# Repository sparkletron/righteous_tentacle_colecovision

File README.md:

# Righteous Tentacle, Colecovision Reverse Engineering Project
### Schematic and PCB reproduction.

---

  author: Jay Convertino

  date: 2023.03.01

  details: Reverse engineer original PCB to create a schematic and functional replacment board. This only includes the NTSC system.

  license: MIT

---

## LICENSE
  - All files related to or generated from the KiCAD source fall under the MIT license.
  - All files generated by me, Jay Convertino, fall under the MIT license.
  - All files from other sources fall under the license of their specification.

## RELEASE VERSIONS
### Current
  - 1.0.2.F - Fixed solder mask on expansion bay connector.

### Past
  - 1.0.1.F - Added power and reset switch to case.
  - 1.0.0.F - initial release of revision F main PCB
  - DEV

## Gerbers
  Files available below, to download select the download icon next to the raw icon on right hand upper side of the page.
  - [Main PCB Gerber Archive](schematic/PCB_TOOLS/gerber/MAIN_GERBER.zip)
  - [RF PCB Gerber Archive](schematic/PCB_TOOLS/gerber/RF_GERBER.zip)

## Wiki
  - Please see the [Wiki](../../wiki) for various information.
    - Contains howto's, build notes, bill of materials, project logs, and signal documentation.

## Parts list
  - [Link to Wiki Parts list for the original console](../../wiki/Detailed-Part-Listing-For-Original)
  - [Link to Wiki Parts list for ordering parts](../../wiki/Detailed-Part-Listing-For-Orders)

## Intro

  This recreation of the PCB is for documenation, and reproduction purposes. This mimicks the PCB of the original NTSC revision F main board.

## SOURCES
### Schematic Check
  - Atari HQ Schematic : https://wiki.console5.com/wiki/Colecovision : Dan Boris
  - Atari Age : https://forums.atariage.com/topic/285656-new-colecovision-schematics/ : ChildOfCV

  Special thanks to ChildOfCV. Using his as a check for mine after buzzing out my own board was a great help. His schematic on
  its own is a great resource.

  Did find a few issues with mine vs the ChildOfCV version, my board is a different revision so they will differ in subtle ways.
  Seems to be mostly just cap and resistor values in the RF circuit. Though I did adjust my values on the clock to reflect those
  recommend in the tech manual.

  The Dan Boris schematic is ok, has a few mistakes that I can't recall at the moment. Mentioning it since I did look at it, but
  due to its issues I didn't use it.

## REQUIREMENTS
  - KiCAD v7.X

## BUILD TIPS
  This design is made so anyone can build this. You may send it out to a fab house, you may use a PCB mill, or even etch it.
  This is possible since the components can serve as the plated through hole. Other holes can simply have a solid piece of
  wire inserted and soldered to complete the connection (excess resistor leads is a great option).

  Recommend soldering the cartridge connector first, the CPU makes soldering one side of the pins a bit difficult to do
  without melting the connector.

  There are various questionable routings, these are how the original is done. Some adjustments were made to make some things easier
  for at home builders without plated through holes.

## FILE INFORMATION
  - README.md, is this file.
  - LICENSE.md, is the license file (MIT) for anything create by me, Jay Convertion, that resides in this repository.
  - doc, contains various documents used.
    - datasheets, contains parts used on the original board.
    - refs, sources used for checks
      - Coleco_ADAM_Schematic_-_Delta_Game.png, publicly available schematic of the ADAM
      - Coleco.zip, ChildOfCV schematic for the console and other various parts of the colecovision.
      - colecovision_atari_hq_schematic.pdf, Colecovision console schematic... has errors.
      - tms-doc-annotated.pdf, TMS design document corrected by Nicholas Piegdon
  - models, PCB items and case designes
    - component_search_engine, website 3D files
    - FreeCAD
      - MainBoard, 3D PCB export to step using freecad instead of kicad.
      - parts, parts designed for the PCB by myself and future contributions.
    - inventor_2024
      - base_case, contains ipt/stl files for building a case for the colecovision.
      - OldVersions, inventor files
    - partcommunity, website 3D files
    - kicad, kicad 3D pcb export to step.
  - pics, images take by me or others(watermark added) of the colecovision.
    - 3D, images generated by modeling tools.
    - built, contains all PCBs built
    - build_case, contains all completed cases with PCB.
    - control_pcb, pics of a different Colecovision console pcb (different REV) for comparison.
    - control_unit, pics of a different Colecovision console for comparison.
    - outside_sources, external sources with added watermark.
    - reverse_high_res, scans from a Canon 9600 DPI flatbed scanner of the PCB boards. Compressed to save space.
    - tear_down, images of the parts as they came apart.
    - signals
      - digital, all digital analyzer captures
      - analog, all analog scope captures
  - schematic, contains KiCAD schematic files.
    - coleco_original.kicad_pro, this file is the main project file that contains EVERTHING.
    - *-backups, are folders KiCAD creates to backup the project.
    - PCB_TOOLS
      - gerber, containts all exports from KiCAD
        - main, base PCB
        - rf, modulator PCB
      - GIMP_Placement_Tool, gimp project used to help place parts in the correct locations.
      - main, contains the main PCB extracted from the main project for production.
      - rf, contains RF PCB extracted from the main project for production.
    - lib, external components for KiCAD
      - CONNECTOR_PCBEdge_EXT
      - LOGOS
      - MHPS2273
      - MODELS
      - MOUNTS
      - OS102011MA1QN1
      - PADS
      - POWER_SYMBOLS
      - RCJ-041
      - RF_MODULATORS
      - SWITCHES_THT
      - TE_550841-2
      - VARIABLE_INDUCTORS
      - VINTAGE_AUDIO_SYNTH
      - VINTAGE_RAM
      - VINTAGE_VDP
    - PDF, various KiCAD exports in the PDF format. PCB and/or schematics.

## PCB IMAGE

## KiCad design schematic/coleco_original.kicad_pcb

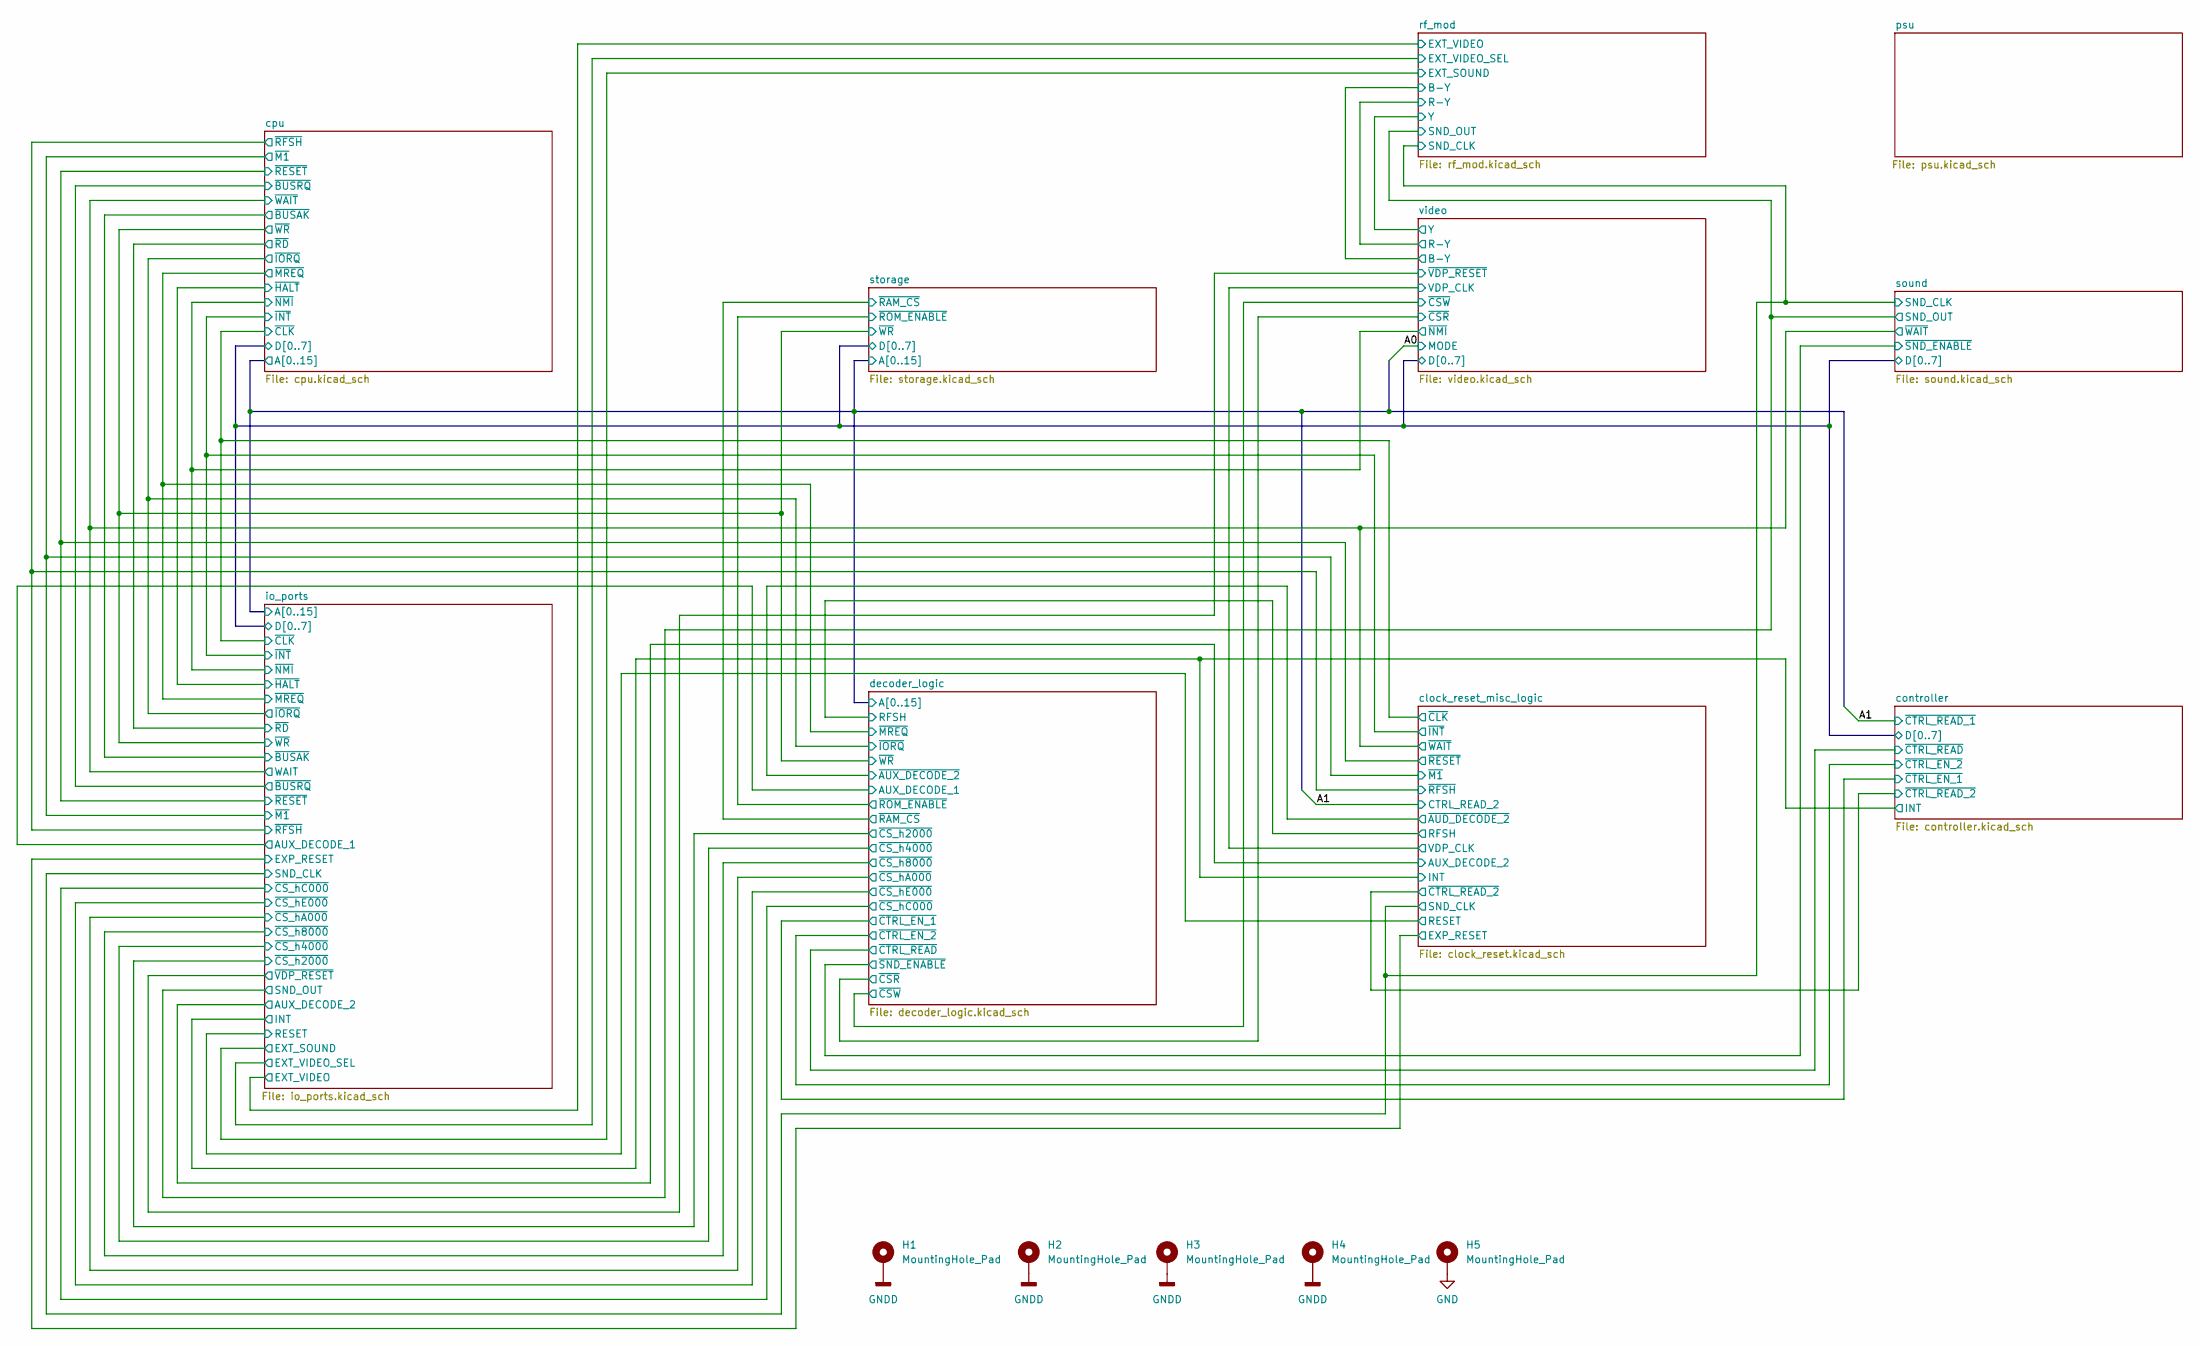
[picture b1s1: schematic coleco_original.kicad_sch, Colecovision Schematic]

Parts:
H1, H2, H3, H4, H5: MountingHole_Pad; MountingHole_5.3mm_M5_ISO14580_Pad

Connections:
GND: H5.1; also elsewhere on the board
GNDD: H1.1, H2.1, H3.1, H4.1; also elsewhere on the board

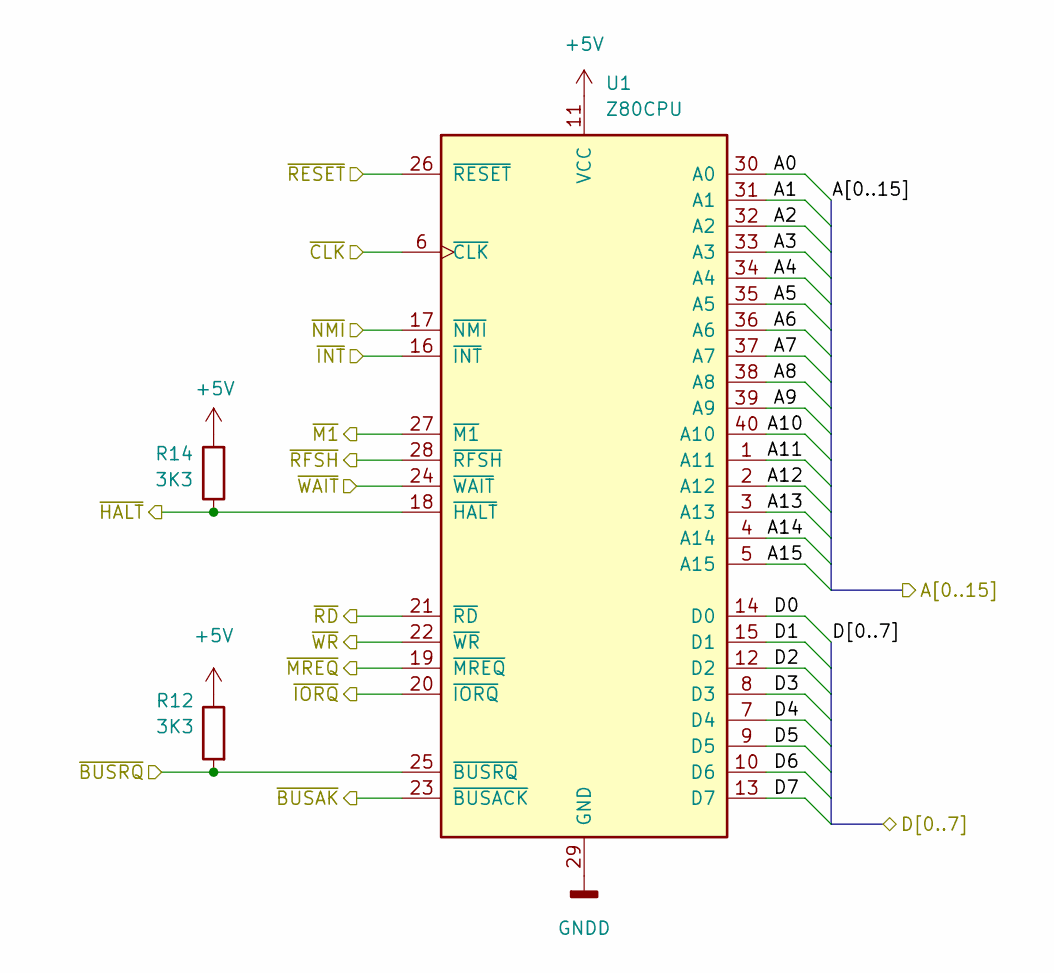
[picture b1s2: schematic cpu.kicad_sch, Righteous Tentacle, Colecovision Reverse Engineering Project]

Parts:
R12, R14: 3K3; R_Axial_DIN0207_L6.3mm_D2.5mm_P10.16mm_Horizontal
U1: Z80CPU; DIP-40_W15.24mm_LongPads

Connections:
+5V: R12.1, R14.2, U1.11 (VCC); also elsewhere on the board
/clock_reset_misc_logic/~CLK: U1.6 (~CLK); also elsewhere on the board
/clock_reset_misc_logic/~INT: U1.16 (~INT); also elsewhere on the board
/clock_reset_misc_logic/~M1: U1.27 (~M1); also elsewhere on the board
/clock_reset_misc_logic/~RESET: U1.26 (~RESET); also elsewhere on the board
/clock_reset_misc_logic/~RFSH: U1.28 (~RFSH); also elsewhere on the board
/clock_reset_misc_logic/~WAIT: U1.24 (~WAIT); also elsewhere on the board
/cpu/A0: U1.30 (A0); also elsewhere on the board
/cpu/A1: U1.31 (A1); also elsewhere on the board
/cpu/A2: U1.32 (A2); also elsewhere on the board
/cpu/A3: U1.33 (A3); also elsewhere on the board
/cpu/A4: U1.34 (A4); also elsewhere on the board
/cpu/A5: U1.35 (A5); also elsewhere on the board
/cpu/A6: U1.36 (A6); also elsewhere on the board
/cpu/A7: U1.37 (A7); also elsewhere on the board
/cpu/A8: U1.38 (A8); also elsewhere on the board
/cpu/A9: U1.39 (A9); also elsewhere on the board
/cpu/A10: U1.40 (A10); also elsewhere on the board
/cpu/A11: U1.1 (A11); also elsewhere on the board
/cpu/A12: U1.2 (A12); also elsewhere on the board
/cpu/A13: U1.3 (A13); also elsewhere on the board
/cpu/A14: U1.4 (A14); also elsewhere on the board
/cpu/A15: U1.5 (A15); also elsewhere on the board
/cpu/D0: U1.14 (D0); also elsewhere on the board
/cpu/D1: U1.15 (D1); also elsewhere on the board
/cpu/D2: U1.12 (D2); also elsewhere on the board
/cpu/D3: U1.8 (D3); also elsewhere on the board
/cpu/D4: U1.7 (D4); also elsewhere on the board
/cpu/D5: U1.9 (D5); also elsewhere on the board
/cpu/D6: U1.10 (D6); also elsewhere on the board
/cpu/D7: U1.13 (D7); also elsewhere on the board
/cpu/~BUSAK: U1.23 (~BUSACK); also elsewhere on the board
/cpu/~BUSRQ: R12.2, U1.25 (~BUSRQ); also elsewhere on the board
/cpu/~HALT: R14.1, U1.18 (~HALT); also elsewhere on the board
/cpu/~IORQ: U1.20 (~IORQ); also elsewhere on the board
/cpu/~MREQ: U1.19 (~MREQ); also elsewhere on the board
/cpu/~NMI: U1.17 (~NMI); also elsewhere on the board
/cpu/~RD: U1.21 (~RD); also elsewhere on the board
/cpu/~WR: U1.22 (~WR); also elsewhere on the board
GNDD: U1.29 (GND); also elsewhere on the board

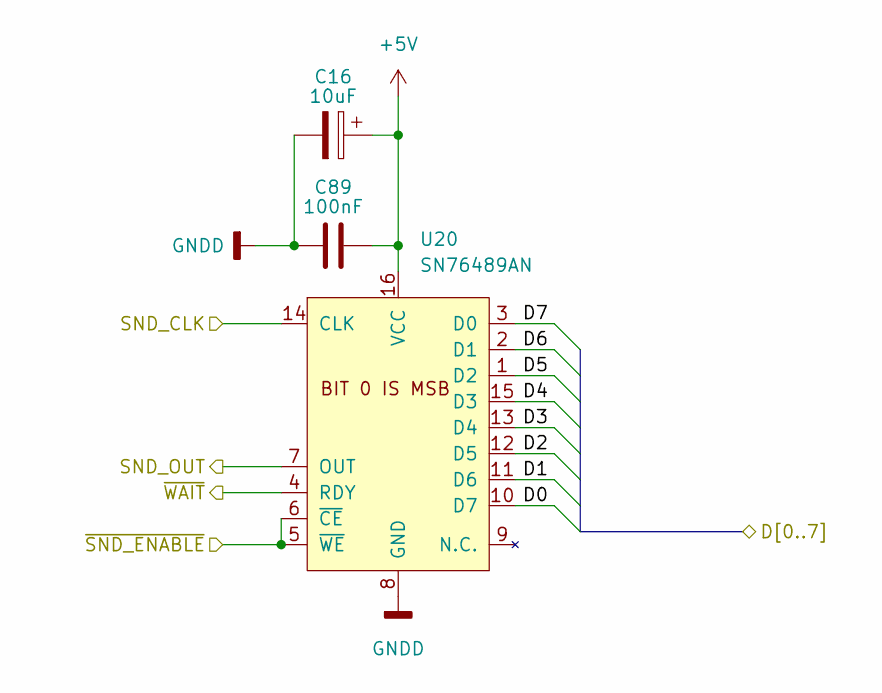
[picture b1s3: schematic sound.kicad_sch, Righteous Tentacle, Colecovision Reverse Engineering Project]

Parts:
C16: 10uF; CP_Radial_D8.0mm_P5.00mm
C89: 100nF; C_Disc_D7.0mm_W2.5mm_P5.00mm
U20: SN76489AN; DIP-16_W7.62mm_LongPads

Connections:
+5V: C16.1, C89.1, U20.16 (VCC); also elsewhere on the board
/clock_reset_misc_logic/SND_CLK: U20.14 (CLK); also elsewhere on the board
/clock_reset_misc_logic/~WAIT: U20.4 (RDY); also elsewhere on the board
/cpu/D0: U20.10 (D7); also elsewhere on the board
/cpu/D1: U20.11 (D6); also elsewhere on the board
/cpu/D2: U20.12 (D5); also elsewhere on the board
/cpu/D3: U20.13 (D4); also elsewhere on the board
/cpu/D4: U20.15 (D3); also elsewhere on the board
/cpu/D5: U20.1 (D2); also elsewhere on the board
/cpu/D6: U20.2 (D1); also elsewhere on the board
/cpu/D7: U20.3 (D0); also elsewhere on the board
/decoder_logic/~SND_ENABLE: U20.5 (~WE), U20.6 (~CE); also elsewhere on the board
/io_ports/SND_OUT: U20.7 (OUT); also elsewhere on the board
GNDD: C16.2, C89.2, U20.8 (GND); also elsewhere on the board

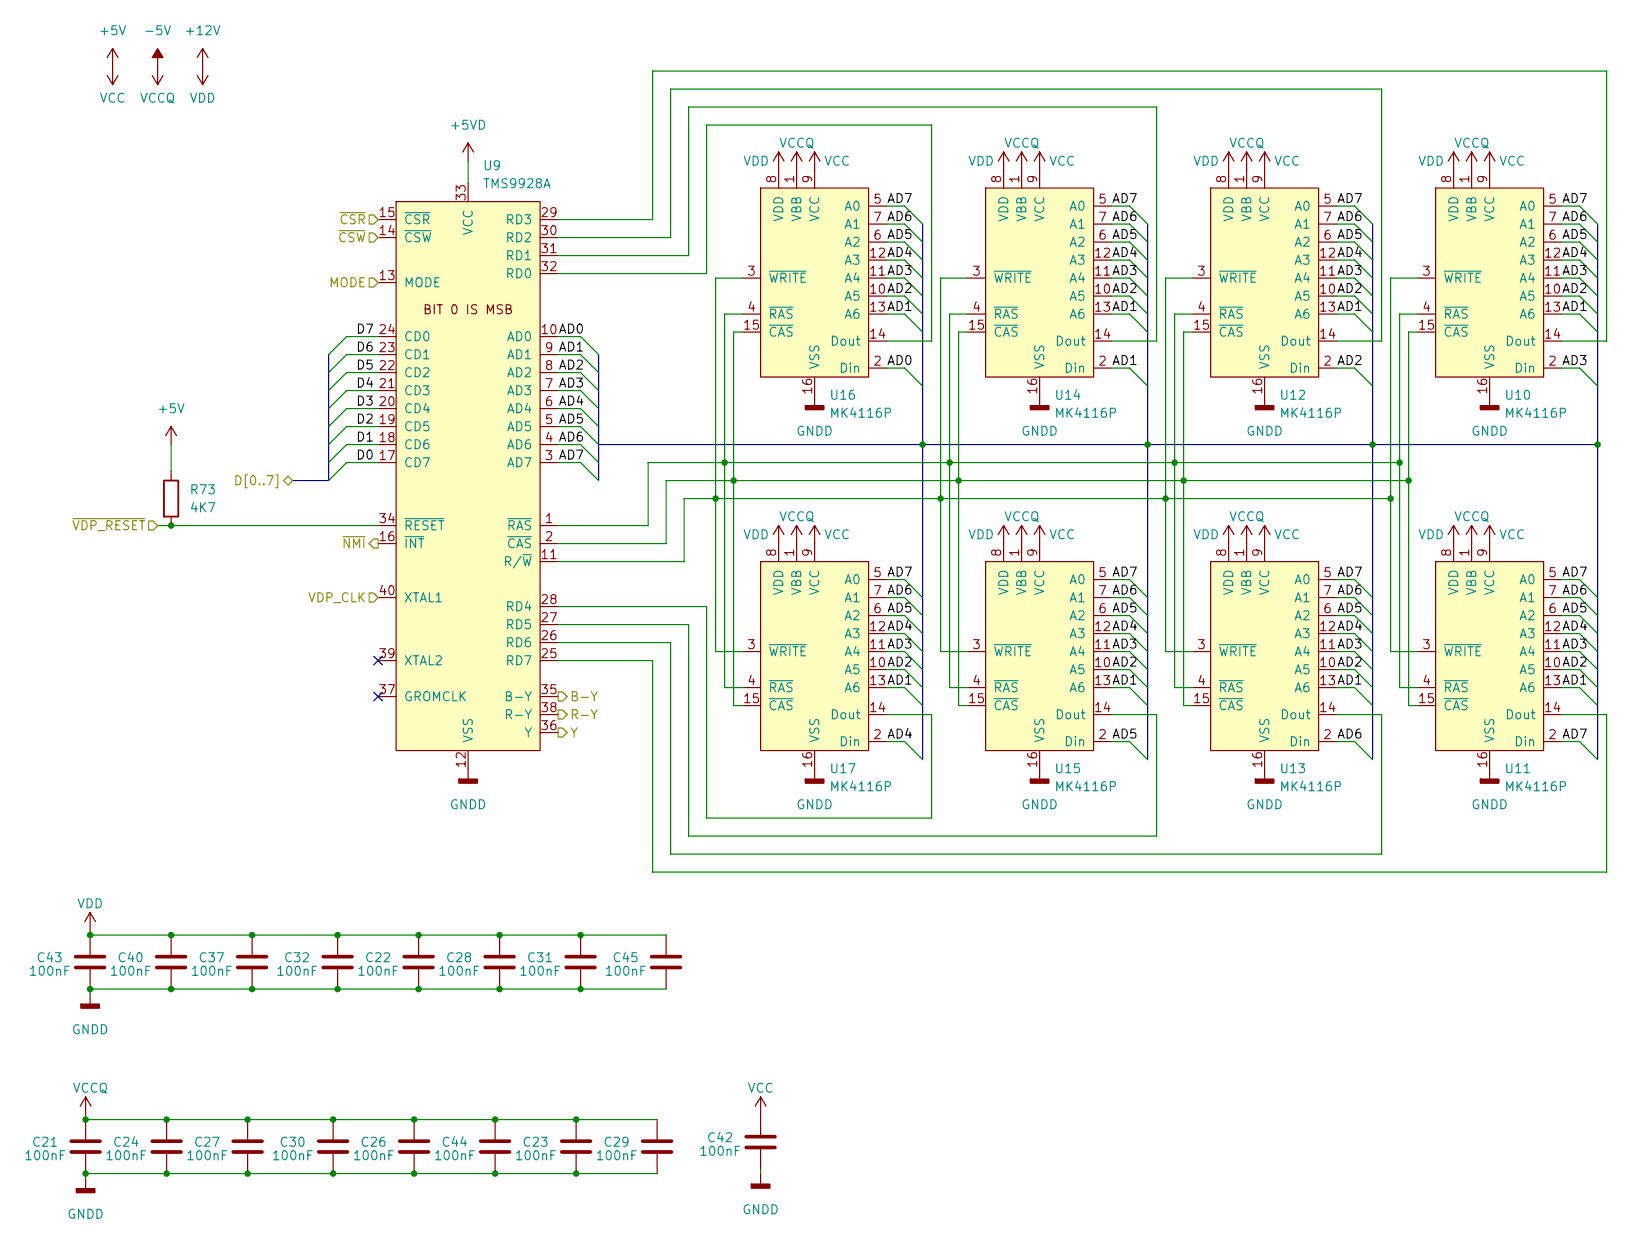
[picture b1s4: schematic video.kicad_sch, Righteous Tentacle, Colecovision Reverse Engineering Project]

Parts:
C21, C22, C23, C24, C26, C27, C28, C29, C30, C31, C32, C37, C40, C42, C43, C44, C45: 100nF; C_Disc_D7.0mm_W2.5mm_P5.00mm
R73: 4K7; R_Axial_DIN0207_L6.3mm_D2.5mm_P10.16mm_Horizontal
U9: TMS9928A; DIP-40_W15.24mm_LongPads
U10, U11, U12, U13, U14, U15, U16, U17: MK4116P; DIP-16_W7.62mm_LongPads

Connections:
+5V: C42.1, R73.1, U10.9 (VCC), U11.9 (VCC), U12.9 (VCC), U13.9 (VCC), U14.9 (VCC), U15.9 (VCC), U16.9 (VCC), U17.9 (VCC); also elsewhere on the board
+5VD: U9.33 (VCC); also elsewhere on the board
+12V: C22.1, C28.1, C31.1, C32.1, C37.1, C40.1, C43.1, C45.1, U10.8 (VDD), U11.8 (VDD), U12.8 (VDD), U13.8 (VDD), U14.8 (VDD), U15.8 (VDD), U16.8 (VDD), U17.8 (VDD); also elsewhere on the board
-5V: C21.1, C23.1, C24.1, C26.1, C27.1, C29.1, C30.1, C44.1, U10.1 (VBB), U11.1 (VBB), U12.1 (VBB), U13.1 (VBB), U14.1 (VBB), U15.1 (VBB), U16.1 (VBB), U17.1 (VBB); also elsewhere on the board
/clock_reset_misc_logic/VDP_CLK: U9.40 (XTAL1); also elsewhere on the board
/cpu/A0: U9.13 (MODE); also elsewhere on the board
/cpu/D0: U9.17 (CD7); also elsewhere on the board
/cpu/D1: U9.18 (CD6); also elsewhere on the board
/cpu/D2: U9.19 (CD5); also elsewhere on the board
/cpu/D3: U9.20 (CD4); also elsewhere on the board
/cpu/D4: U9.21 (CD3); also elsewhere on the board
/cpu/D5: U9.22 (CD2); also elsewhere on the board
/cpu/D6: U9.23 (CD1); also elsewhere on the board
/cpu/D7: U9.24 (CD0); also elsewhere on the board
/cpu/~NMI: U9.16 (~INT); also elsewhere on the board
/decoder_logic/~CSR: U9.15 (~CSR); also elsewhere on the board
/decoder_logic/~CSW: U9.14 (~CSW); also elsewhere on the board
/io_ports/~VDP_RESET: R73.2, U9.34 (~RESET); also elsewhere on the board
/rf_mod/B-Y: U9.35 (B-Y); also elsewhere on the board
/rf_mod/R-Y: U9.38 (R-Y); also elsewhere on the board
/rf_mod/Y: U9.36 (Y); also elsewhere on the board
/video/AD0: U9.10 (AD0), U16.2 (Din)
/video/AD1: U9.9 (AD1), U10.13 (A6), U11.13 (A6), U12.13 (A6), U13.13 (A6), U14.2 (Din), U14.13 (A6), U15.13 (A6), U16.13 (A6), U17.13 (A6)
/video/AD2: U9.8 (AD2), U10.10 (A5), U11.10 (A5), U12.2 (Din), U12.10 (A5), U13.10 (A5), U14.10 (A5), U15.10 (A5), U16.10 (A5), U17.10 (A5)
/video/AD3: U9.7 (AD3), U10.2 (Din), U10.11 (A4), U11.11 (A4), U12.11 (A4), U13.11 (A4), U14.11 (A4), U15.11 (A4), U16.11 (A4), U17.11 (A4)
/video/AD4: U9.6 (AD4), U10.12 (A3), U11.12 (A3), U12.12 (A3), U13.12 (A3), U14.12 (A3), U15.12 (A3), U16.12 (A3), U17.2 (Din), U17.12 (A3)
/video/AD5: U9.5 (AD5), U10.6 (A2), U11.6 (A2), U12.6 (A2), U13.6 (A2), U14.6 (A2), U15.2 (Din), U15.6 (A2), U16.6 (A2), U17.6 (A2)
/video/AD6: U9.4 (AD6), U10.7 (A1), U11.7 (A1), U12.7 (A1), U13.2 (Din), U13.7 (A1), U14.7 (A1), U15.7 (A1), U16.7 (A1), U17.7 (A1)
/video/AD7: U9.3 (AD7), U10.5 (A0), U11.2 (Din), U11.5 (A0), U12.5 (A0), U13.5 (A0), U14.5 (A0), U15.5 (A0), U16.5 (A0), U17.5 (A0)
GNDD: C21.2, C22.2, C23.2, C24.2, C26.2, C27.2, C28.2, C29.2, C30.2, C31.2, C32.2, C37.2, C40.2, C42.2, C43.2, C44.2, C45.2, U9.12 (VSS), U10.16 (VSS), U11.16 (VSS), U12.16 (VSS), U13.16 (VSS), U14.16 (VSS), U15.16 (VSS), U16.16 (VSS), U17.16 (VSS); also elsewhere on the board
unnamed: U9.11 (R/~W), U10.3 (~WRITE), U11.3 (~WRITE), U12.3 (~WRITE), U13.3 (~WRITE), U14.3 (~WRITE), U15.3 (~WRITE), U16.3 (~WRITE), U17.3 (~WRITE)
unnamed: U9.1 (~RAS), U10.4 (~RAS), U11.4 (~RAS), U12.4 (~RAS), U13.4 (~RAS), U14.4 (~RAS), U15.4 (~RAS), U16.4 (~RAS), U17.4 (~RAS)
unnamed: U9.29 (RD3), U10.14 (Dout)
unnamed: U9.2 (~CAS), U10.15 (~CAS), U11.15 (~CAS), U12.15 (~CAS), U13.15 (~CAS), U14.15 (~CAS), U15.15 (~CAS), U16.15 (~CAS), U17.15 (~CAS)
unnamed: U9.25 (RD7), U11.14 (Dout)
unnamed: U9.30 (RD2), U12.14 (Dout)
unnamed: U9.26 (RD6), U13.14 (Dout)
unnamed: U9.31 (RD1), U14.14 (Dout)
unnamed: U9.27 (RD5), U15.14 (Dout)
unnamed: U9.32 (RD0), U16.14 (Dout)
unnamed: U9.28 (RD4), U17.14 (Dout)

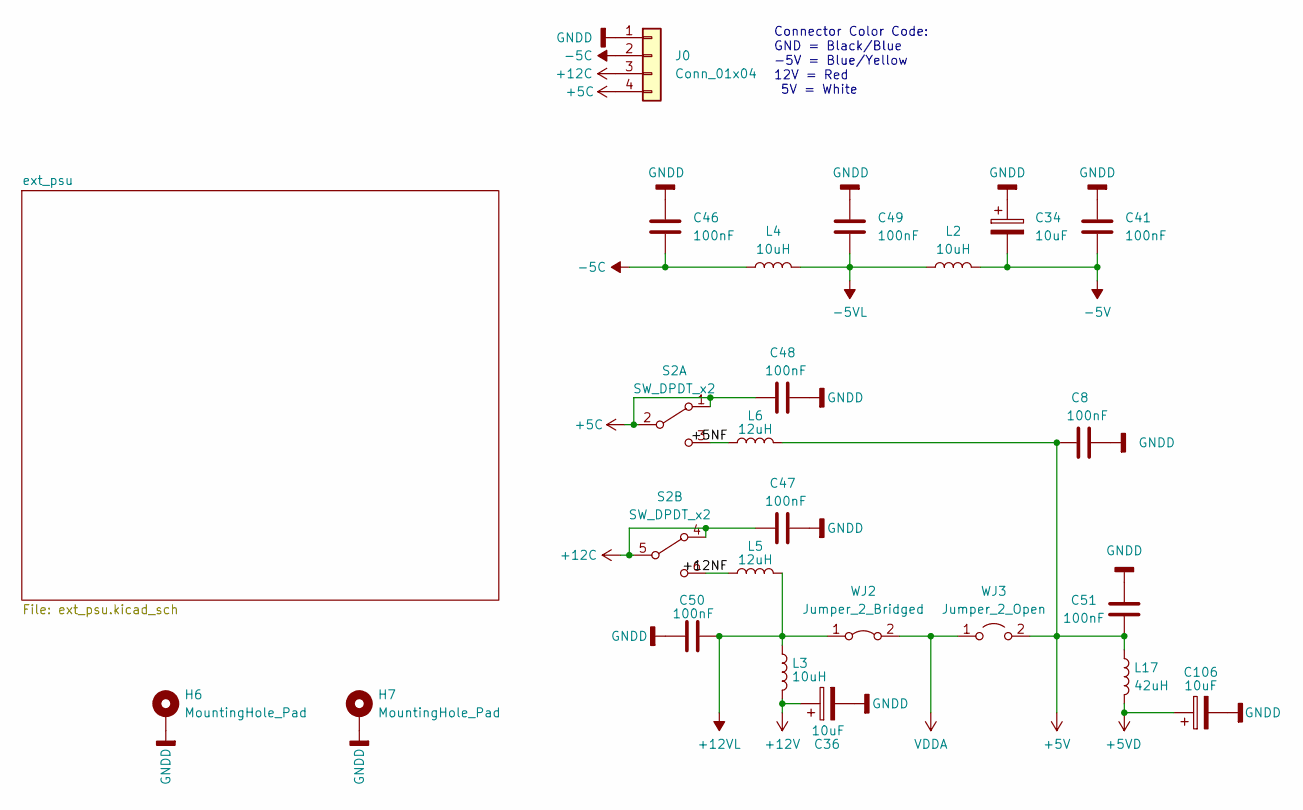
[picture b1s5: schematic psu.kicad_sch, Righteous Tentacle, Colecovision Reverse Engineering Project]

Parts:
C8, C41, C46, C47, C48, C49, C50, C51: 100nF; C_Disc_D7.0mm_W2.5mm_P5.00mm
C34, C36: 10uF; CP_Radial_D8.0mm_P5.00mm
C106: 10uF; CP_Radial_Tantal_D4.5mm_P2.50mm
H6, H7: MountingHole_Pad; SWITCH_MOUNT
J0: Conn_01x04; Molex_KK-396_A-41791-0004_1x04_P3.96mm_Vertical
L2, L3, L4: 10uH; L_Axial_L11.0mm_D4.5mm_P7.62mm_Vertical_Fastron_MECC
L5, L6: 12uH; L_Axial_L12.8mm_D5.8mm_P25.40mm_Horizontal_Fastron_HBCC
L17: 42uH; L_Axial_L11.0mm_D4.5mm_P7.62mm_Vertical_Fastron_MECC
S2: SW_DPDT_x2; DPDT_GF-626-0061
WJ2: Jumper_2_Bridged; R_Axial_DIN0207_L6.3mm_D2.5mm_P15.24mm_Horizontal
WJ3: Jumper_2_Open; R_Axial_DIN0207_L6.3mm_D2.5mm_P15.24mm_Horizontal

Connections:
+5C: C48.2, J0.4, S2.1 (A), S2.2 (B)
+5V: C8.2, C51.1, L6.2, L17.1, WJ3.2 (B); also elsewhere on the board
+5VD: C106.1, L17.2; also elsewhere on the board
+12C: C47.2, J0.3, S2.4 (A), S2.5 (B)
+12V: C36.1, L3.2; also elsewhere on the board
+12VL: C50.2, L3.1, L5.2, WJ2.1 (A); also elsewhere on the board
-5C: C46.2, J0.2, L4.1
-5V: C34.2, C41.2, L2.2; also elsewhere on the board
-5VL: C49.2, L2.1, L4.2; also elsewhere on the board
/psu/+5NF: L6.1, S2.3 (C)
/psu/+12NF: L5.1, S2.6 (C)
GNDD: C8.1, C34.1, C36.2, C41.1, C46.1, C47.1, C48.1, C49.1, C50.1, C51.2, C106.2, H6.1, H7.1, J0.1; also elsewhere on the board
VDDA: WJ2.2 (B), WJ3.1 (A); also elsewhere on the board

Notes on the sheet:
Connector Color Code: GND = Black/Blue -5V = Blue/Yellow 12V = Red 5V = White

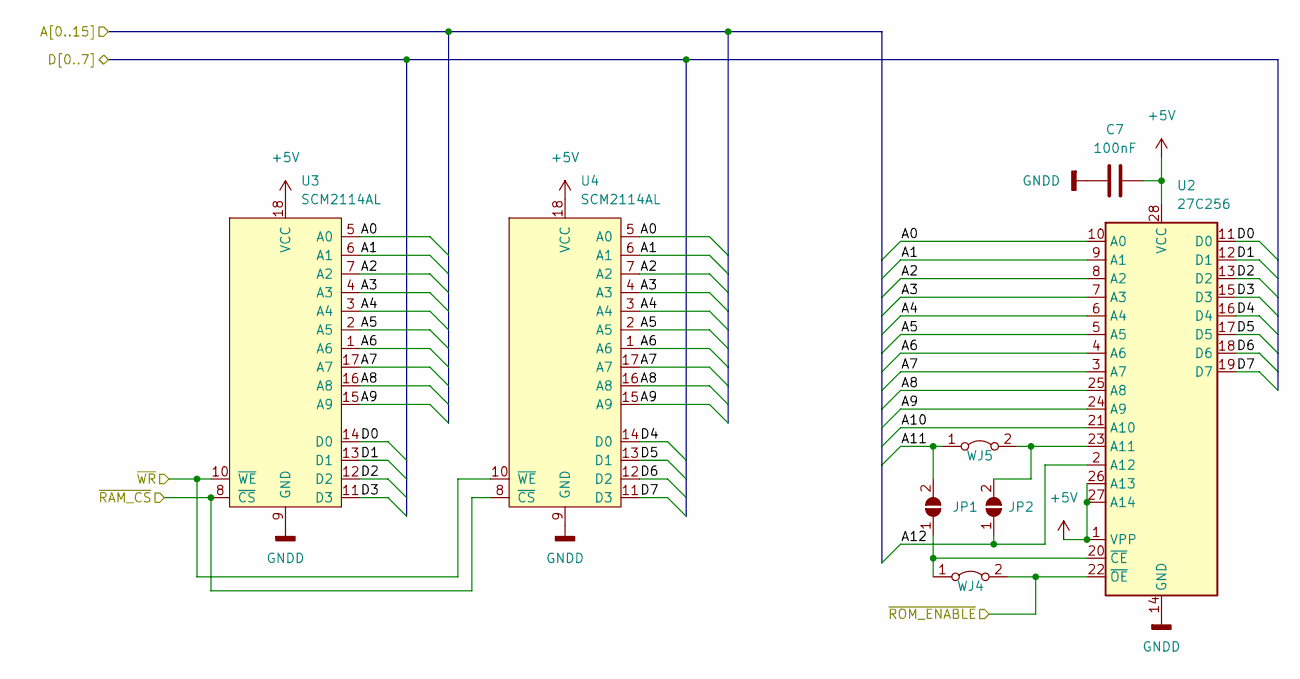
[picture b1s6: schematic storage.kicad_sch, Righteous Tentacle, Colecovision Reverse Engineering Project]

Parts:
C7: 100nF; C_Disc_D7.0mm_W2.5mm_P5.00mm
JP1, JP2: SolderJumper_2_Open; SolderJumper-2_P1.3mm_Open_Pad1.0x1.5mm
U2: 27C256; DIP-28_W15.24mm
U3, U4: SCM2114AL; DIP-18_W7.62mm_LongPads
WJ4, WJ5: Jumper_2_Bridged_32K_ROM; R_Axial_DIN0207_L6.3mm_D2.5mm_P15.24mm_Horizontal

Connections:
+5V: C7.1, U2.1 (VPP), U2.26 (A13), U2.27 (A14), U2.28 (VCC), U3.18 (VCC), U4.18 (VCC); also elsewhere on the board
/cpu/A0: U2.10 (A0), U3.5 (A0), U4.5 (A0); also elsewhere on the board
/cpu/A1: U2.9 (A1), U3.6 (A1), U4.6 (A1); also elsewhere on the board
/cpu/A2: U2.8 (A2), U3.7 (A2), U4.7 (A2); also elsewhere on the board
/cpu/A3: U2.7 (A3), U3.4 (A3), U4.4 (A3); also elsewhere on the board
/cpu/A4: U2.6 (A4), U3.3 (A4), U4.3 (A4); also elsewhere on the board
/cpu/A5: U2.5 (A5), U3.2 (A5), U4.2 (A5); also elsewhere on the board
/cpu/A6: U2.4 (A6), U3.1 (A6), U4.1 (A6); also elsewhere on the board
/cpu/A7: U2.3 (A7), U3.17 (A7), U4.17 (A7); also elsewhere on the board
/cpu/A8: U2.25 (A8), U3.16 (A8), U4.16 (A8); also elsewhere on the board
/cpu/A9: U2.24 (A9), U3.15 (A9), U4.15 (A9); also elsewhere on the board
/cpu/A10: U2.21 (A10); also elsewhere on the board
/cpu/A11: JP1.2 (B), WJ5.1 (A); also elsewhere on the board
/cpu/A12: JP2.1 (A), U2.2 (A12); also elsewhere on the board
/cpu/D0: U2.11 (D0), U3.14 (D0); also elsewhere on the board
/cpu/D1: U2.12 (D1), U3.13 (D1); also elsewhere on the board
/cpu/D2: U2.13 (D2), U3.12 (D2); also elsewhere on the board
/cpu/D3: U2.15 (D3), U3.11 (D3); also elsewhere on the board
/cpu/D4: U2.16 (D4), U4.14 (D0); also elsewhere on the board
/cpu/D5: U2.17 (D5), U4.13 (D1); also elsewhere on the board
/cpu/D6: U2.18 (D6), U4.12 (D2); also elsewhere on the board
/cpu/D7: U2.19 (D7), U4.11 (D3); also elsewhere on the board
/cpu/~WR: U3.10 (~WE), U4.10 (~WE); also elsewhere on the board
/decoder_logic/~RAM_CS: U3.8 (~CS), U4.8 (~CS); also elsewhere on the board
/decoder_logic/~ROM_ENABLE: U2.22 (~OE), WJ4.2 (B); also elsewhere on the board
GNDD: C7.2, U2.14 (GND), U3.9 (GND), U4.9 (GND); also elsewhere on the board
unnamed: JP1.1 (A), U2.20 (~CE), WJ4.1 (A)
unnamed: JP2.2 (B), U2.23 (A11), WJ5.2 (B)

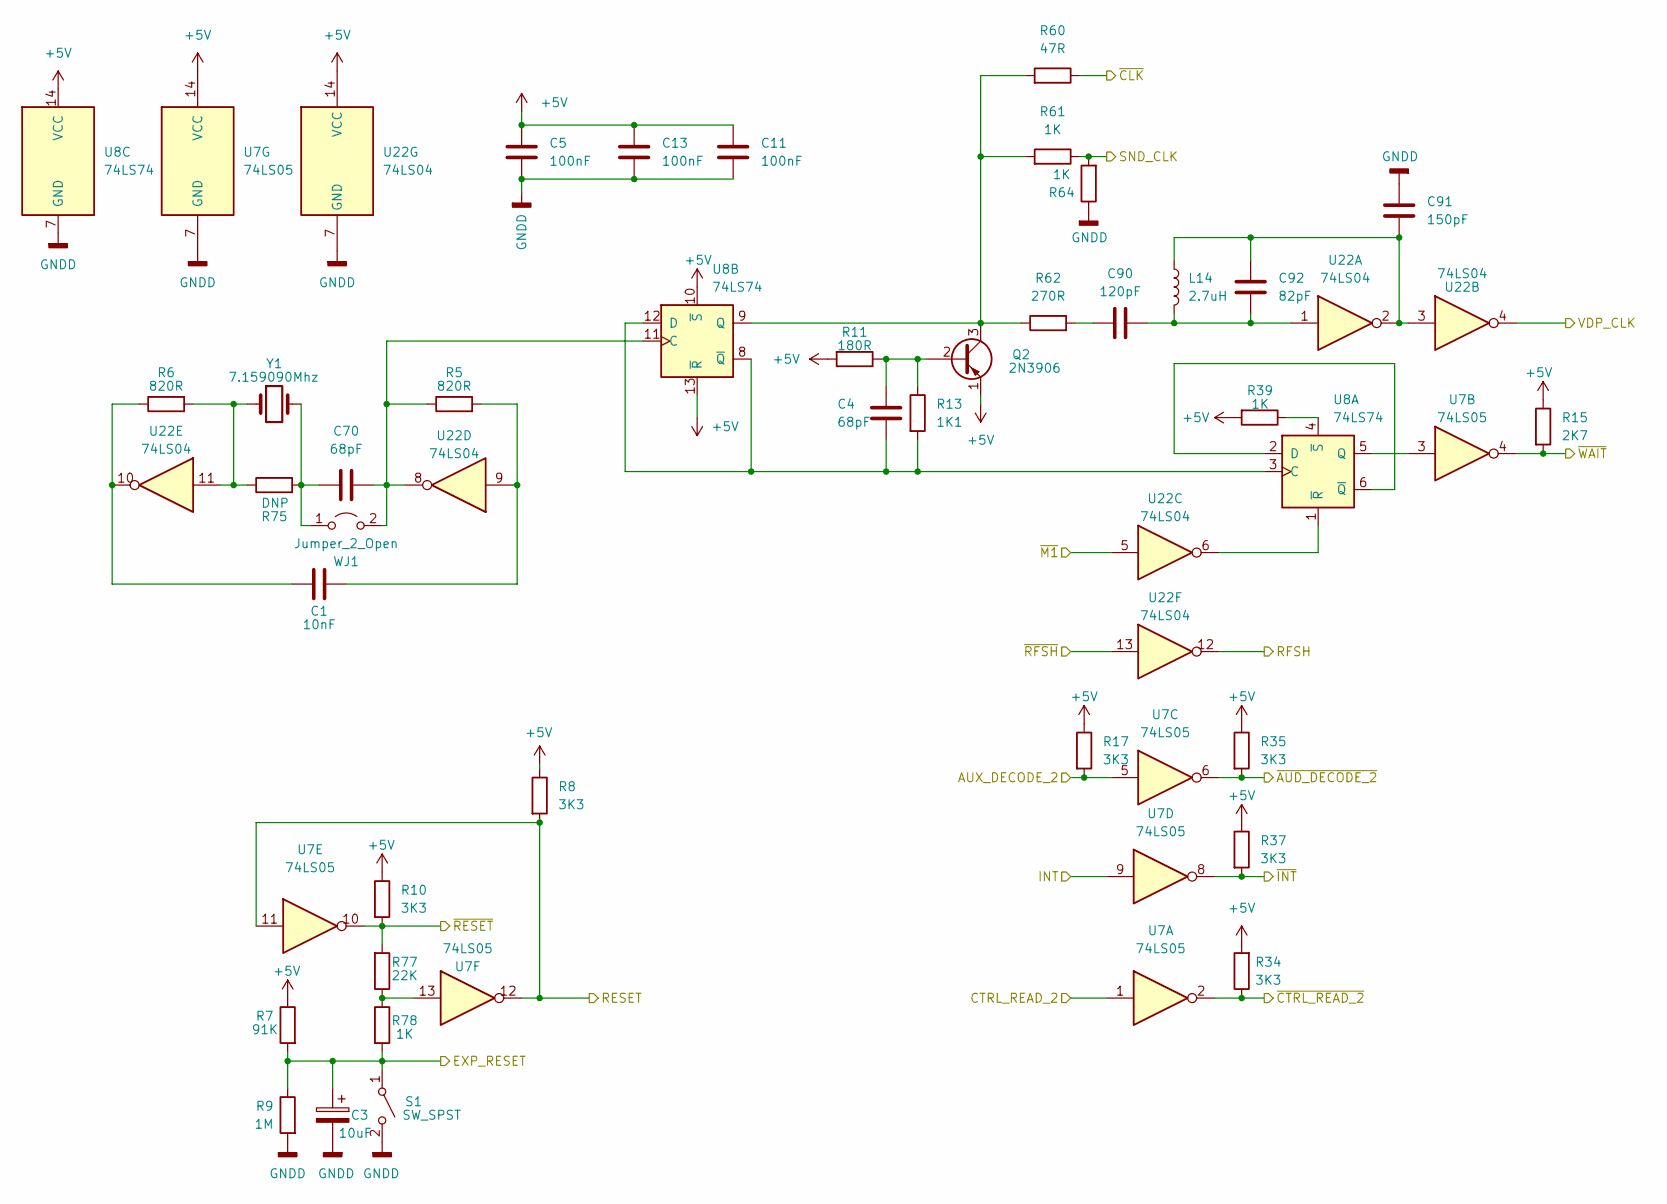
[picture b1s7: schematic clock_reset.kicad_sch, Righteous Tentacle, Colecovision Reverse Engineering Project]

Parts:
C1: 10nF; C_Disc_D7.0mm_W2.5mm_P5.00mm
C3: 10uF; CP_Radial_D8.0mm_P5.00mm
C4, C70: 68pF; C_Disc_D7.0mm_W2.5mm_P5.00mm
C5, C11, C13: 100nF; C_Disc_D7.0mm_W2.5mm_P5.00mm
C90: 120pF; C_Disc_D7.0mm_W2.5mm_P5.00mm
C91: 150pF; C_Disc_D7.0mm_W2.5mm_P5.00mm
C92: 82pF; C_Disc_D7.0mm_W2.5mm_P5.00mm
L14: 2.7uH; L_Axial_L11.0mm_D4.5mm_P7.62mm_Vertical_Fastron_MECC
Q2: 2N3906; TO-92_Wide
R5, R6: 820R; R_Axial_DIN0207_L6.3mm_D2.5mm_P10.16mm_Horizontal
R7: 91K; R_Axial_DIN0207_L6.3mm_D2.5mm_P10.16mm_Horizontal
R8, R10, R17, R34, R35, R37: 3K3; R_Axial_DIN0207_L6.3mm_D2.5mm_P10.16mm_Horizontal
R9: 1M; R_Axial_DIN0207_L6.3mm_D2.5mm_P10.16mm_Horizontal
R11: 180R; R_Axial_DIN0207_L6.3mm_D2.5mm_P10.16mm_Horizontal
R13: 1K1; R_Axial_DIN0207_L6.3mm_D2.5mm_P10.16mm_Horizontal
R15: 2K7; R_Axial_DIN0207_L6.3mm_D2.5mm_P10.16mm_Horizontal
R39, R61, R64, R78: 1K; R_Axial_DIN0207_L6.3mm_D2.5mm_P10.16mm_Horizontal
R60: 47R; R_Axial_DIN0207_L6.3mm_D2.5mm_P10.16mm_Horizontal
R62: 270R; R_Axial_DIN0207_L6.3mm_D2.5mm_P10.16mm_Horizontal
R75: DNP; R_Axial_DIN0207_L6.3mm_D2.5mm_P10.16mm_Horizontal
R77: 22K; R_Axial_DIN0207_L6.3mm_D2.5mm_P10.16mm_Horizontal
S1: SW_SPST; Coleco_RST
U7: 74LS05; DIP-14_W7.62mm_LongPads
U8: 74LS74; DIP-14_W7.62mm_LongPads
U22: 74LS04; DIP-14_W7.62mm_LongPads
WJ1: Jumper_2_Open; R_Axial_DIN0207_L6.3mm_D2.5mm_P15.24mm_Horizontal
Y1: 7.159090Mhz; Crystal_HC49-U_Vertical

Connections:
+5V: C5.2, C11.2, C13.2, Q2.1 (E), R7.1, R8.1, R10.1, R11.2, R15.1, R17.1, R34.2, R35.1, R37.1, R39.2, U7.14 (VCC), U8.10 (~S), U8.13 (~R), U8.14 (VCC), U22.14 (VCC); also elsewhere on the board
/clock_reset_misc_logic/AUX_DECODE_2: R17.2, U7.5; also elsewhere on the board
/clock_reset_misc_logic/EXP_RESET: C3.1, R7.2, R9.1, R78.2, S1.1 (A); also elsewhere on the board
/clock_reset_misc_logic/INT: U7.9; also elsewhere on the board
/clock_reset_misc_logic/RESET: R8.2, U7.11, U7.12; also elsewhere on the board
/clock_reset_misc_logic/RFSH: U22.12; also elsewhere on the board
/clock_reset_misc_logic/SND_CLK: R61.1, R64.2; also elsewhere on the board
/clock_reset_misc_logic/VDP_CLK: U22.4; also elsewhere on the board
/clock_reset_misc_logic/~AUD_DECODE_2: R35.2, U7.6; also elsewhere on the board
/clock_reset_misc_logic/~CLK: R60.1; also elsewhere on the board
/clock_reset_misc_logic/~CTRL_READ_2: R34.1, U7.2; also elsewhere on the board
/clock_reset_misc_logic/~INT: R37.2, U7.8; also elsewhere on the board
/clock_reset_misc_logic/~M1: U22.5; also elsewhere on the board
/clock_reset_misc_logic/~RESET: R10.2, R77.2, U7.10; also elsewhere on the board
/clock_reset_misc_logic/~RFSH: U22.13; also elsewhere on the board
/clock_reset_misc_logic/~WAIT: R15.2, U7.4; also elsewhere on the board
/cpu/A1: U7.1; also elsewhere on the board
GNDD: C3.2, C5.1, C11.1, C13.1, C91.1, R9.2, R64.1, S1.2 (B), U7.7 (GND), U8.7 (GND), U22.7 (GND); also elsewhere on the board
unnamed: C1.1, R6.1, U22.10
unnamed: C1.2, R5.2, U22.9
unnamed: C4.1, Q2.2 (B), R11.1, R13.1
unnamed: C4.2, R13.2, U8.3 (C), U8.8 (~Q), U8.12 (D)
unnamed: C70.1, R5.1, U8.11 (C), U22.8, WJ1.2 (B)
unnamed: C70.2, R75.2, WJ1.1 (A), Y1.2
unnamed: C90.1, R62.2
unnamed: C90.2, C92.2, L14.2, U22.1
unnamed: C91.2, C92.1, L14.1, U22.2, U22.3
unnamed: Q2.3 (C), R60.2, R61.2, R62.1, U8.9 (Q)
unnamed: R6.2, R75.1, U22.11, Y1.1
unnamed: R39.1, U8.4 (~S)
unnamed: R77.1, R78.1, U7.13
unnamed: U7.3, U8.5 (Q)
unnamed: U8.2 (D), U8.6 (~Q)
unnamed: U8.1 (~R), U22.6
